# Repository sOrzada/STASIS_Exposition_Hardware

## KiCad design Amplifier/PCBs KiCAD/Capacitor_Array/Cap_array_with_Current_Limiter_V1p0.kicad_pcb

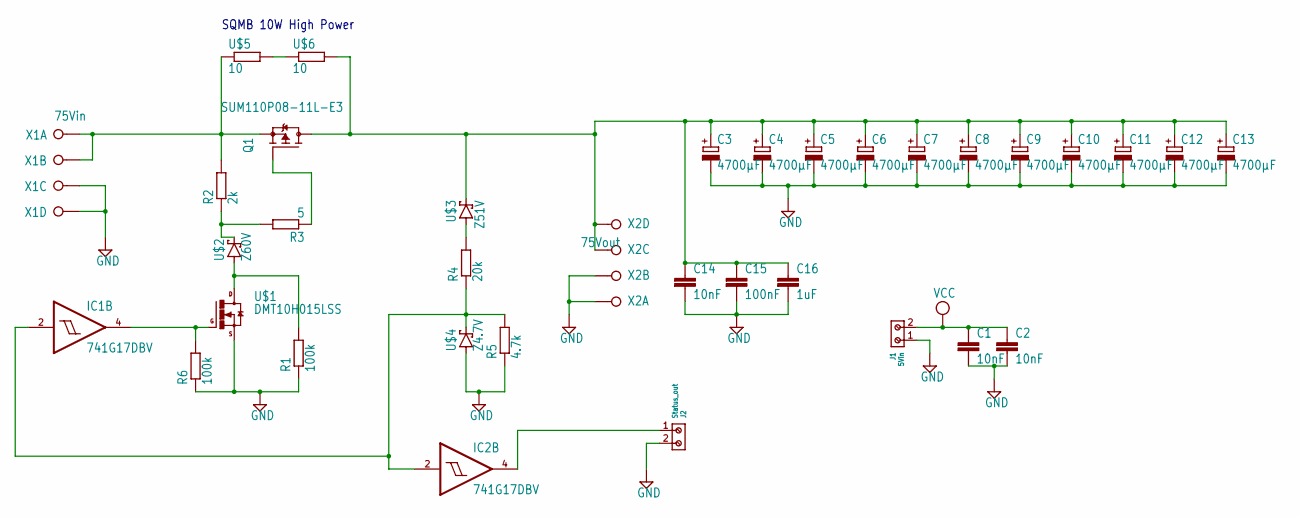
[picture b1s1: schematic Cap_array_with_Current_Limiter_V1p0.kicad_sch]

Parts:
C1, C2: 10nF; C0805
C3, C4, C5, C6, C7, C8, C9, C10, C11, C12, C13: 4700µF; EB30D
C14: 10nF; C1206
C15: 100nF; C1206
C16: 1uF; C1206
IC1, IC2: 741G17DBV; SOT23-5
J1: 5Vin; 691210910002
J2: Status_out; 691210910002
Q1: SUM110P08-11L-E3; TO263
R1, R6: 100k; R0805
R2: 2k; R2512
R3: 5; R0805
R4: 20k; R0805
R5: 4.7k; R0805
U$1: DMT10H015LSS; SOIC8
U$2: Z60V; DO-214AA
U$3: Z51V; DO-214AA
U$4: Z4.7V; DO-214AA
U$5, U$6: 10; SQMB
X1: 75Vin; W237-4P
X2: 75Vout; W237-4P

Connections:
GND: C1.2, C2.2, C3.-, C4.-, C5.-, C6.-, C7.-, C8.-, C9.-, C10.-, C11.-, C12.-, C13.-, C14.2, C15.2, C16.2, IC1.3 (GND), IC2.3 (GND), J1.1, J2.2, R1.1, R5.1, R6.1, U$1.1 (S), U$1.2 (S), U$1.3 (S), U$4.A, X1.3, X1.4, X2.1, X2.2
unnamed: R2.1, R3.2, U$2.C
unnamed: Q1.2 (S), R2.2, U$5.P$1 (1), X1.1, X1.2
unnamed: U$5.P$2 (2), U$6.P$1 (1)
unnamed: IC1.4 (O), R6.2, U$1.4 (G)
unnamed: Q1.1 (G), R3.1
unnamed: C3.+, C4.+, C5.+, C6.+, C7.+, C8.+, C9.+, C10.+, C11.+, C12.+, C13.+, C14.1, C15.1, C16.1, Q1.3 (D), U$3.C, U$6.P$2 (2), X2.3, X2.4
unnamed: R4.2, U$3.A
unnamed: IC1.2 (I), IC2.2 (I), R4.1, R5.2, U$4.C
unnamed: IC2.4 (O), J2.1
unnamed: R1.2, U$1.5 (D), U$1.6 (D), U$1.7 (D), U$1.8 (D), U$2.A
VCC: C1.1, C2.1, IC1.5 (VCC), IC2.5 (VCC), J1.2

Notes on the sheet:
SQMB 10W High Power

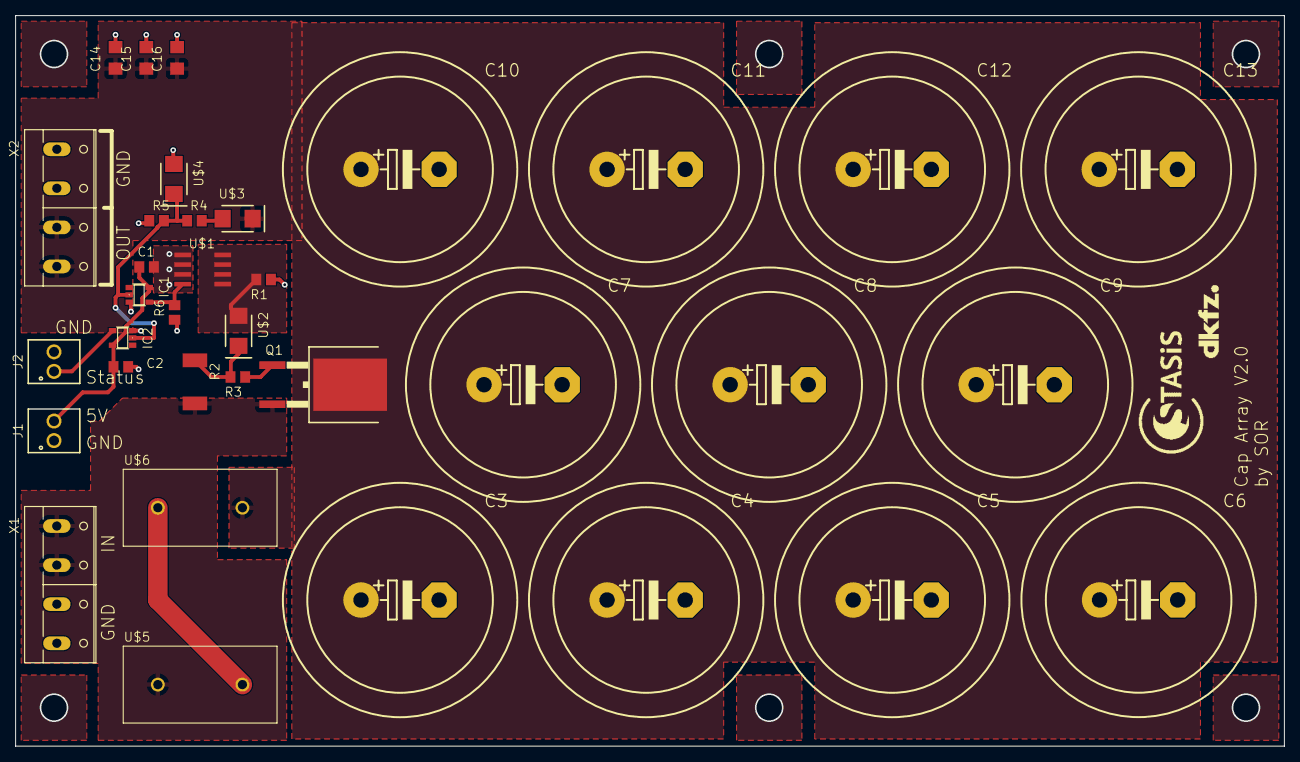
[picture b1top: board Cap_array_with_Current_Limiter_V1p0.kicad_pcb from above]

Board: 2 copper layers, 165.0 x 95.0 mm, 37 parts (0 on the bottom side), 12 nets.

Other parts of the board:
U$7: LOGO_STASIS
U$8: LOGO_DKFZ

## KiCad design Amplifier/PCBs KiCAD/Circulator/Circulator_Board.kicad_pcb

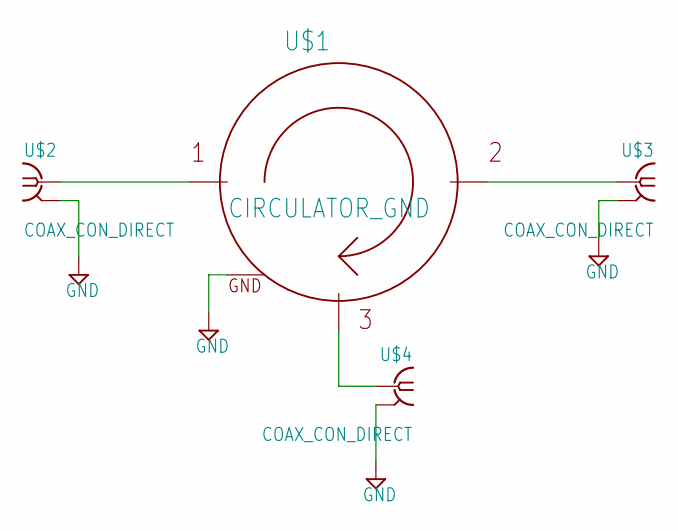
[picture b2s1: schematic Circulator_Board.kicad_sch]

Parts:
U$1: CIRCULATOR_GND; JCD0126T0130LC100
U$2, U$3, U$4: COAX_CON_DIRECT; COAX.141

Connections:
GND: U$1.P$1 (P$GND), U$1.P$2 (P$GND), U$1.P$3 (P$GND), U$1.P$4 (P$GND), U$2.P$2 (GND@1), U$3.P$2 (GND@1), U$4.P$2 (GND@1)
unnamed: U$1.P$IN, U$2.P$1 (1)
unnamed: U$1.P$OUT, U$3.P$1 (1)
unnamed: U$1.P$LOAD, U$4.P$1 (1)

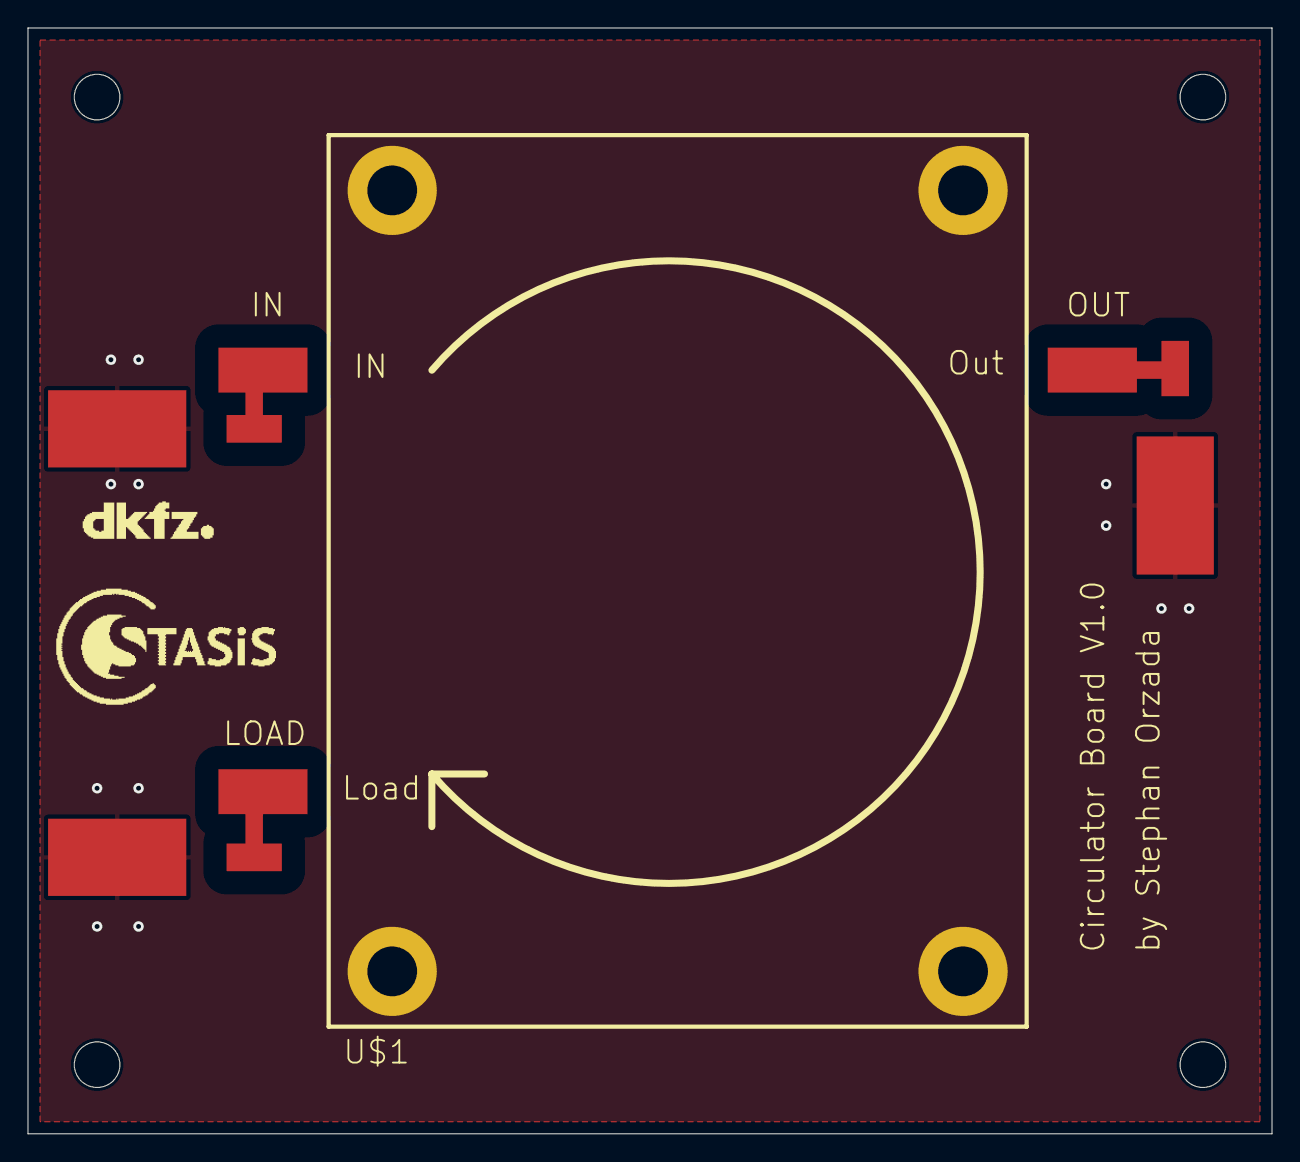
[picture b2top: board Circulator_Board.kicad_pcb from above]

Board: 2 copper layers, 90.0 x 80.0 mm, 10 parts (0 on the bottom side), 4 nets.

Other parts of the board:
@HOLE0, @HOLE1, @HOLE2, @HOLE3: (no value)
U$5: LOGO_DKFZ
U$6: LOGO_STASIS

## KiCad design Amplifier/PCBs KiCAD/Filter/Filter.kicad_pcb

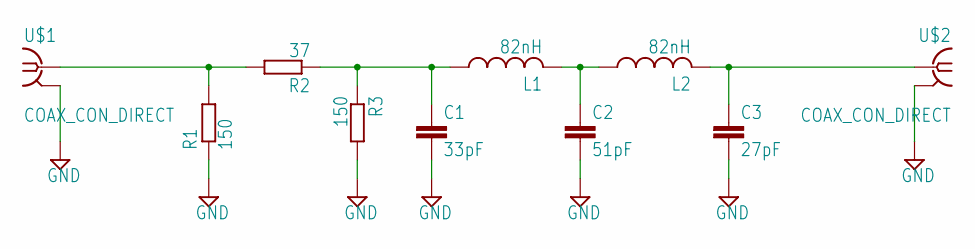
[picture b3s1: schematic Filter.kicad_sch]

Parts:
C1: 33pF; C0805
C2: 51pF; C0805
C3: 27pF; C0805
L1, L2: 82nH; L2012C
R1, R3: 150; R0805
R2: 37; R0805
U$1, U$2: COAX_CON_DIRECT; COAX.141

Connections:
GND: C1.2, C2.2, C3.2, R1.1, R3.2, U$1.P$2 (GND@1), U$2.P$2 (GND@1)
unnamed: C3.1, L2.2, U$2.P$1 (1)
unnamed: C2.1, L1.2, L2.1
unnamed: C1.1, L1.1, R2.1, R3.1
unnamed: R1.2, R2.2, U$1.P$1 (1)

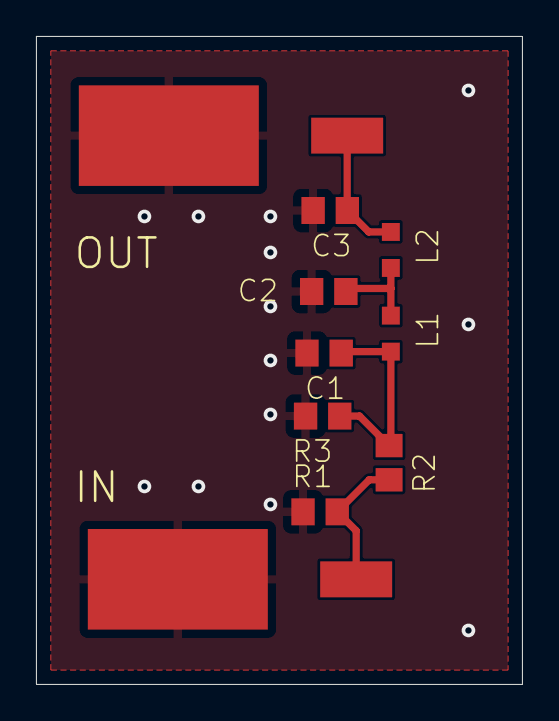
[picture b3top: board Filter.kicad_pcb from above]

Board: 2 copper layers, 27.0 x 36.0 mm, 10 parts (0 on the bottom side), 5 nets.

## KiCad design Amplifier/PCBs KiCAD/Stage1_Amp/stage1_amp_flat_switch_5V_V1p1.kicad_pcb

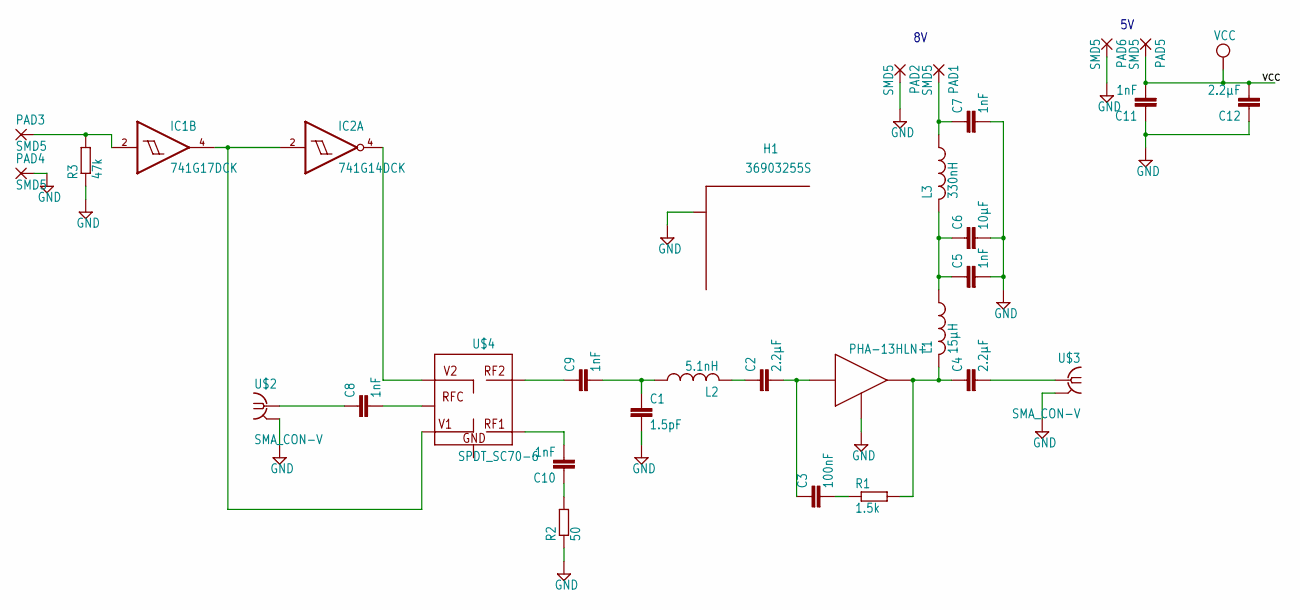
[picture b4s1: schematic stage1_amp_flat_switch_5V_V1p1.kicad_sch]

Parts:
C1: 1.5pF; C0402
C2, C4, C12: 2.2µF; C0402
C3: 100nF; C0402
C5, C7, C8, C9, C10, C11: 1nF; C0402
C6: 10µF; C0805
H1: 36903255S; WE-SHC_ONE-PIECE_36903255S
IC1: 741G17DCK; SC70-5
IC2: 741G14DCK; SC70-5
L1: 15µH; L3225M
L2: 5.1nH; L2012C
L3: 330nH; L3225M
PAD1, PAD2, PAD3, PAD4, PAD5, PAD6: SMD5; SMD2,54-5,08
R1: 1.5k; R0402
R2: 50; R0402
R3: 47k; R0805
U$1: PHA-13HLN+; SOT89
U$2, U$3: SMA_CON-V; BU-SMA-V
U$4: SPDT_SC70-6; SC70-6

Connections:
GND: C1.2, C5.2, C6.2, C7.2, C11.1, C12.1, H1.1, H1.2, H1.3, H1.4, H1.5, H1.6, H1.7, H1.8, H1.9, H1.10, H1.11, H1.12, H1.13, H1.14, H1.15, H1.16, H1.17, H1.18, H1.19, H1.20, IC1.3 (GND), IC2.3 (GND), PAD2.1, PAD4.1, PAD6.1, R2.1, R3.1, U$1.2 (GND), U$1.2@1 (GND), U$2.2 (GND@1), U$2.3 (GND@1), U$2.4 (GND@1), U$2.5 (GND@1), U$3.2 (GND@1), U$3.3 (GND@1), U$3.4 (GND@1), U$3.5 (GND@1)
unnamed: C2.1, L2.2
unnamed: C2.2, C3.1, U$1.1 (IN)
unnamed: C4.1, L1.2, R1.2, U$1.3 (OUT)
unnamed: C1.1, C9.2, L2.1
unnamed: C3.2, R1.1
unnamed: C4.2, U$3.1
unnamed: C5.1, C6.1, L1.1, L3.2
unnamed: C7.1, L3.1, PAD1.1
unnamed: C8.2, U$4.5 (RFC)
unnamed: C8.1, U$2.1
unnamed: C9.1, U$4.3 (RF2)
unnamed: C10.2, U$4.1 (RF1)
unnamed: C10.1, R2.2
unnamed: IC1.4 (O), IC2.2 (I), U$4.6 (V1)
unnamed: IC2.4 (O), U$4.4 (V2)
unnamed: IC1.2 (I), PAD3.1, R3.2
VCC: C11.2, C12.2, IC1.5 (VCC), IC2.5 (VCC), PAD5.1

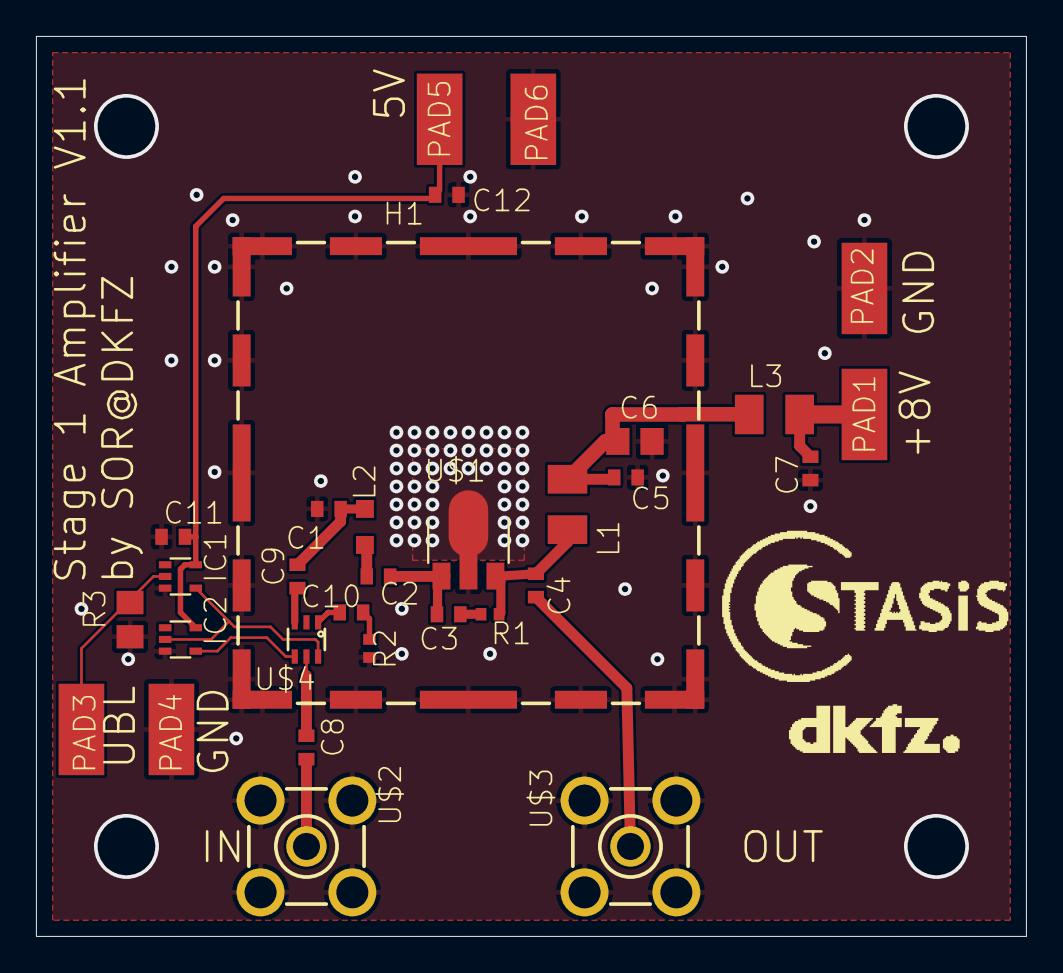
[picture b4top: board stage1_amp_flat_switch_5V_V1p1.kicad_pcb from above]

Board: 2 copper layers, 55.0 x 50.0 mm, 33 parts (0 on the bottom side), 18 nets.

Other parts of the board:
U$5: LOGO_DKFZ
U$6: LOGO_STASIS

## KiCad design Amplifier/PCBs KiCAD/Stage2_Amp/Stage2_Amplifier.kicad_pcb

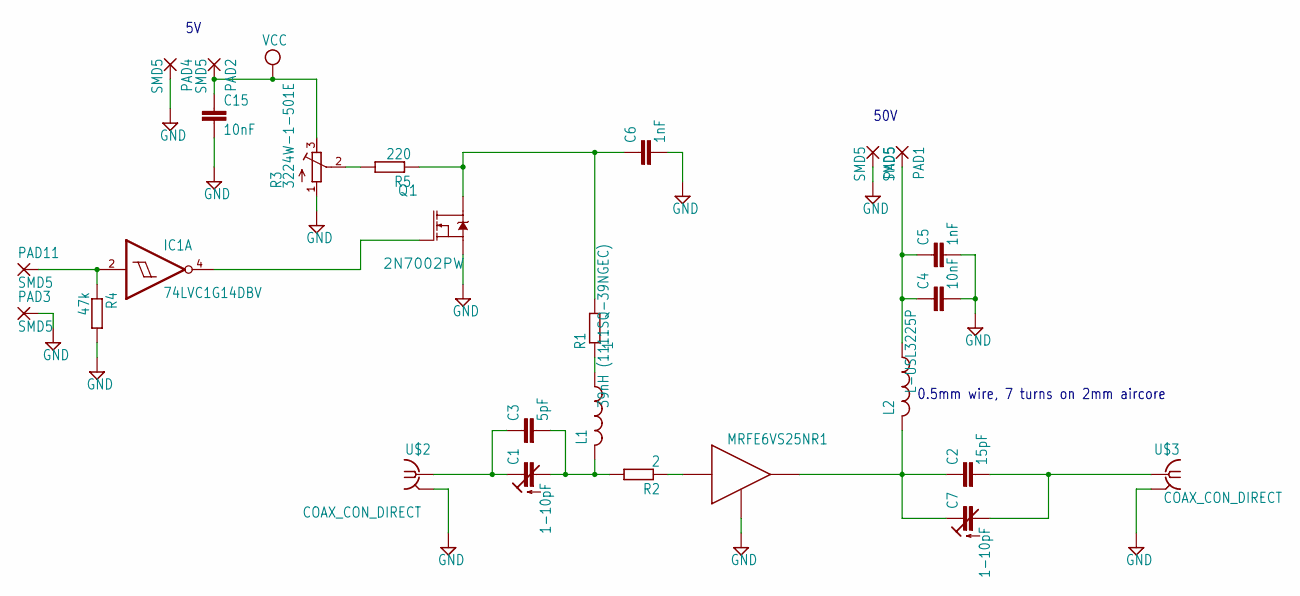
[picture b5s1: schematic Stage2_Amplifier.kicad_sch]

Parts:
C1, C7: 1-10pF; CTRIMTZBX4
C2: 15pF; C1210
C3: 5pF; C1210
C4: 10nF; C1206
C5: 1nF; C1206
C6: 1nF; C0805
C15: 10nF; C0805
IC1: 74LVC1G14DBV; SOT23-5
L1: 39nH (1111SQ-39NGEC); L3225P
L2: L-USL3225P; L3225P
PAD1, PAD2, PAD3, PAD4, PAD5, PAD11: SMD5; SMD2,54-5,08
Q1: 2N7002PW; SOT323
R1: 1; R1206
R2: 2; R1206
R3: 3224W-1-501E; RTRIM3224W
R4: 47k; R0805
R5: 220; R0805
U$1: MRFE6VS25NR1; TO-270_ONBOARD
U$2, U$3: COAX_CON_DIRECT; COAX.141

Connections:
GND: C4.2, C5.2, C6.2, C15.2, IC1.3 (GND), PAD3.1, PAD4.1, PAD5.1, Q1.2 (S), R3.1 (A), R4.2, U$1.P$3 (GND), U$2.P$2 (GND@1), U$3.P$2 (GND@1)
unnamed: R2.1, U$1.P$2 (IN)
unnamed: C1.2 (A), C3.2, L1.2, R2.2
unnamed: L1.1, R1.1
unnamed: C2.1, C7.1 (E), L2.2, U$1.P$1 (OUT)
unnamed: C1.1 (E), C3.1, U$2.P$1 (1)
unnamed: C2.2, C7.2 (A), U$3.P$1 (1)
unnamed: C4.1, C5.1, L2.1, PAD1.1
unnamed: C6.1, Q1.3 (D), R1.2, R5.1
unnamed: R3.2 (S), R5.2
unnamed: IC1.4 (O), Q1.1 (G)
unnamed: IC1.2 (I), PAD11.1, R4.1
VCC: C15.1, IC1.5 (VCC), PAD2.1, R3.3 (E)

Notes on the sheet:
50V
0.5mm wire, 7 turns on 2mm aircore

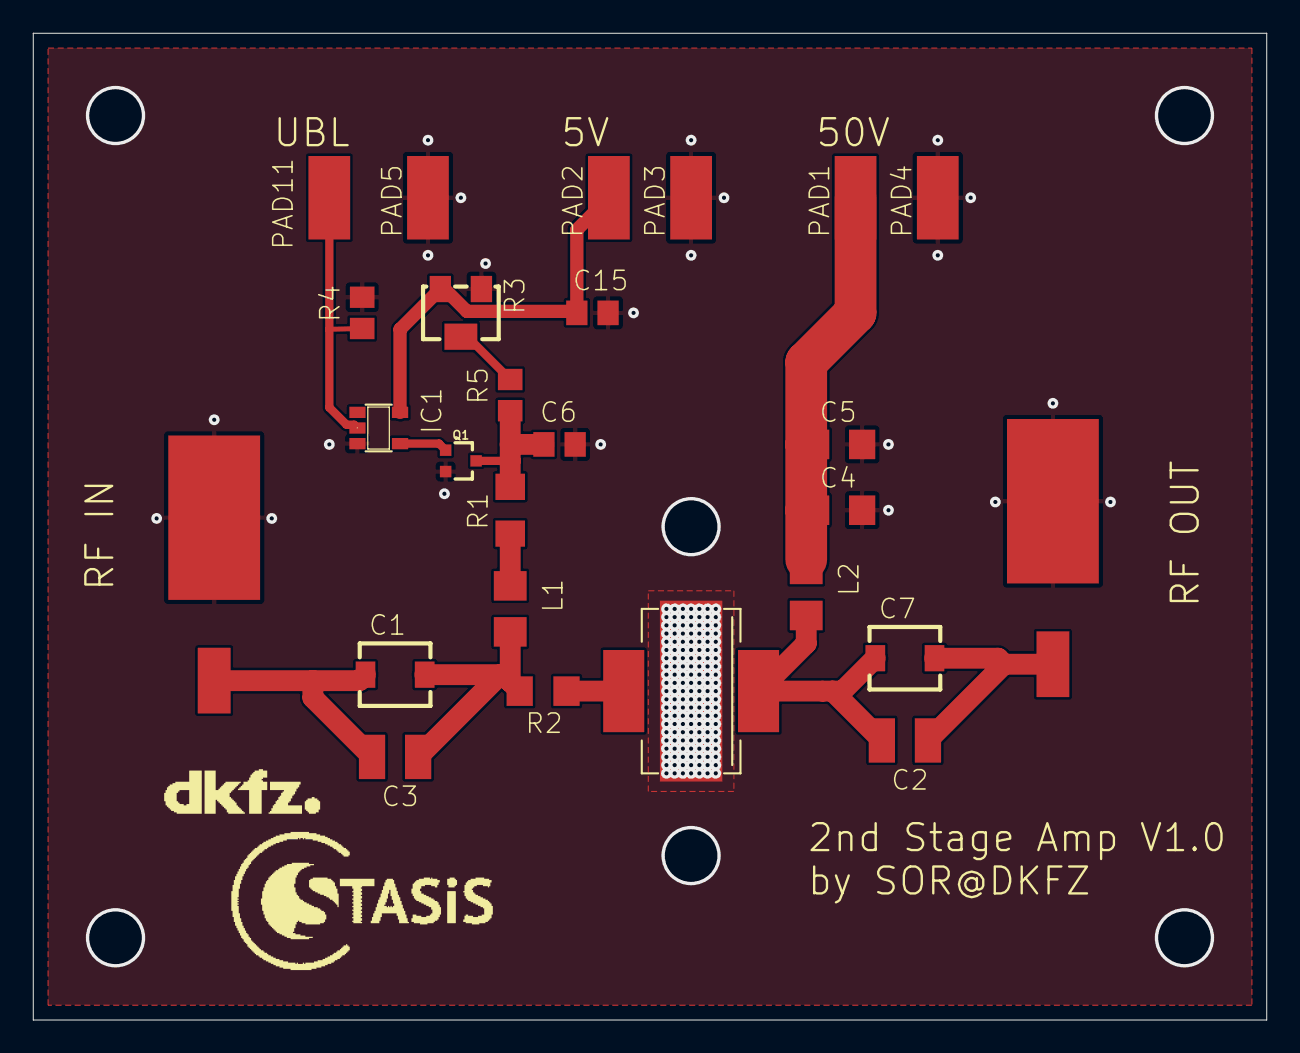
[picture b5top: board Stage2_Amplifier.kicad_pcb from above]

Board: 2 copper layers, 75.0 x 60.0 mm, 28 parts (0 on the bottom side), 13 nets.

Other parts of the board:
U$4: LOGO_STASIS
U$5: LOGO_DKFZ

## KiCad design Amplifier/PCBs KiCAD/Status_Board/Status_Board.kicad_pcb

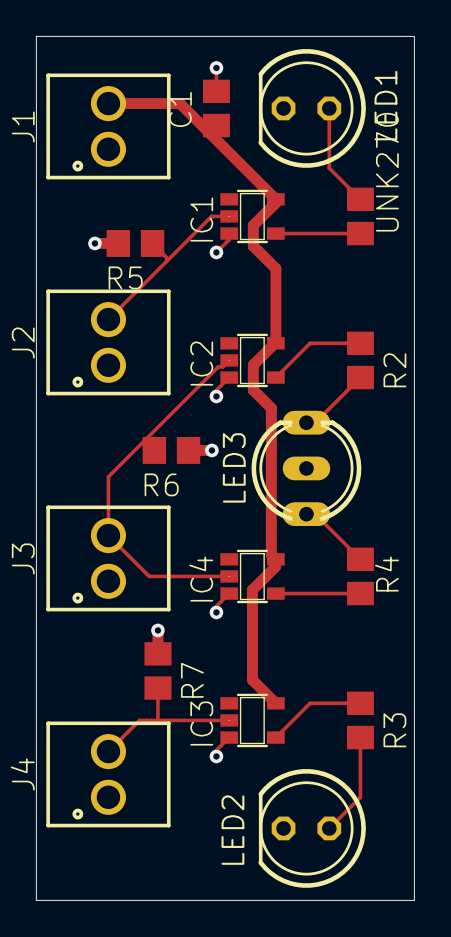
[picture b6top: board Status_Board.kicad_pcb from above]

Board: 2 copper layers, 21.0 x 48.0 mm, 19 parts (0 on the bottom side), 13 nets.

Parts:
C1: 10nF; C0805_334
IC1, IC2, IC3: 74LVC1G17DBV; SOT23-5_87
IC4: 74LVC1G14DBV; SOT23-5_87
J1: 5V; 691210910002_16280519
J2: 75V_Status; 691210910002_16280519
J3: Amp_State; 691210910002_16280519
J4: UBL; 691210910002_16280519
LED1, LED2: LED5MM_259
LED3: DUOLED-C-5MM_259
R2, R3: 220; R0805_334
R4: 180; R0805_334
R5, R6, R7: 47k; R0805_334
UNK270: R0805_334

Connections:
GND: C1.2, IC1.3, IC2.3, IC3.3, IC4.3, J1.1, J2.1, J3.1, J4.1, LED1.K, LED2.K, LED3.C, R5.2, R6.1, R7.1
unnamed: IC4.4, R4.1
unnamed: IC1.2, J2.2, R5.1
unnamed: IC2.2, IC4.2, J3.2, R6.2
unnamed: IC3.2, J4.2, R7.2
unnamed: IC1.4, UNK270.1
unnamed: IC2.4, R2.1
unnamed: IC3.4, R3.1
unnamed: LED1.A, UNK270.2
unnamed: LED3.AR, R2.2
unnamed: LED2.A, R3.2
unnamed: LED3.AX, R4.2
VCC: C1.1, IC1.5, IC2.5, IC3.5, IC4.5, J1.2

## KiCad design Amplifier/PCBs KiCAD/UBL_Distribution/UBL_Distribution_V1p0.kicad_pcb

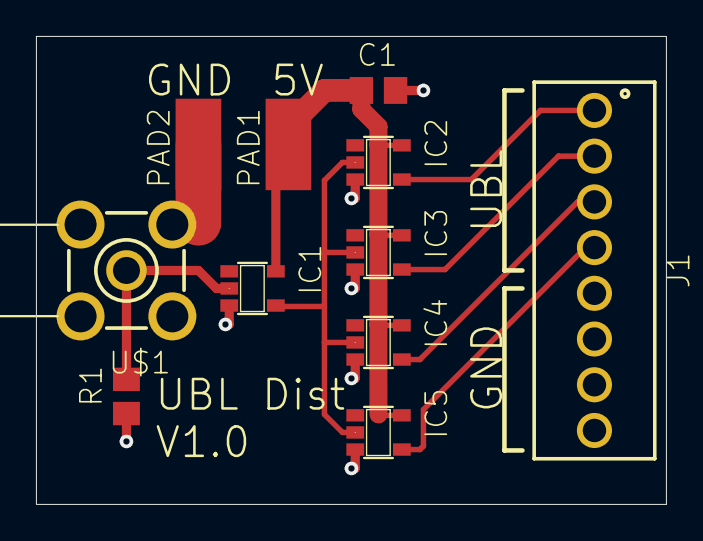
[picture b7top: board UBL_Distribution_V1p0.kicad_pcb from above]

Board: 2 copper layers, 35.0 x 26.0 mm, 11 parts (0 on the bottom side), 8 nets.

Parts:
C1: 10nF; C0805_334
IC1, IC2, IC3, IC4, IC5: 74LVC1G17DBV; SOT23-5_87
J1: Unblank; 691210910008_16280519
PAD1: 5V; SMD2,54-5,08_412
PAD2: GND; SMD2,54-5,08_412
R1: 47k; R0805_334
U$1: SMA_CON-H; BU-SMA-H

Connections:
GND: C1.2, IC1.3, IC2.3, IC3.3, IC4.3, IC5.3, J1.5, J1.6, J1.7, J1.8, PAD2.1, R1.1, U$1.2, U$1.3, U$1.4, U$1.5
unnamed: IC1.2, R1.2, U$1.1
unnamed: IC1.4, IC2.2, IC3.2, IC4.2, IC5.2
unnamed: IC2.4, J1.1
unnamed: IC3.4, J1.2
unnamed: IC4.4, J1.3
unnamed: IC5.4, J1.4
VCC: C1.1, IC1.5, IC2.5, IC3.5, IC4.5, IC5.5, PAD1.1

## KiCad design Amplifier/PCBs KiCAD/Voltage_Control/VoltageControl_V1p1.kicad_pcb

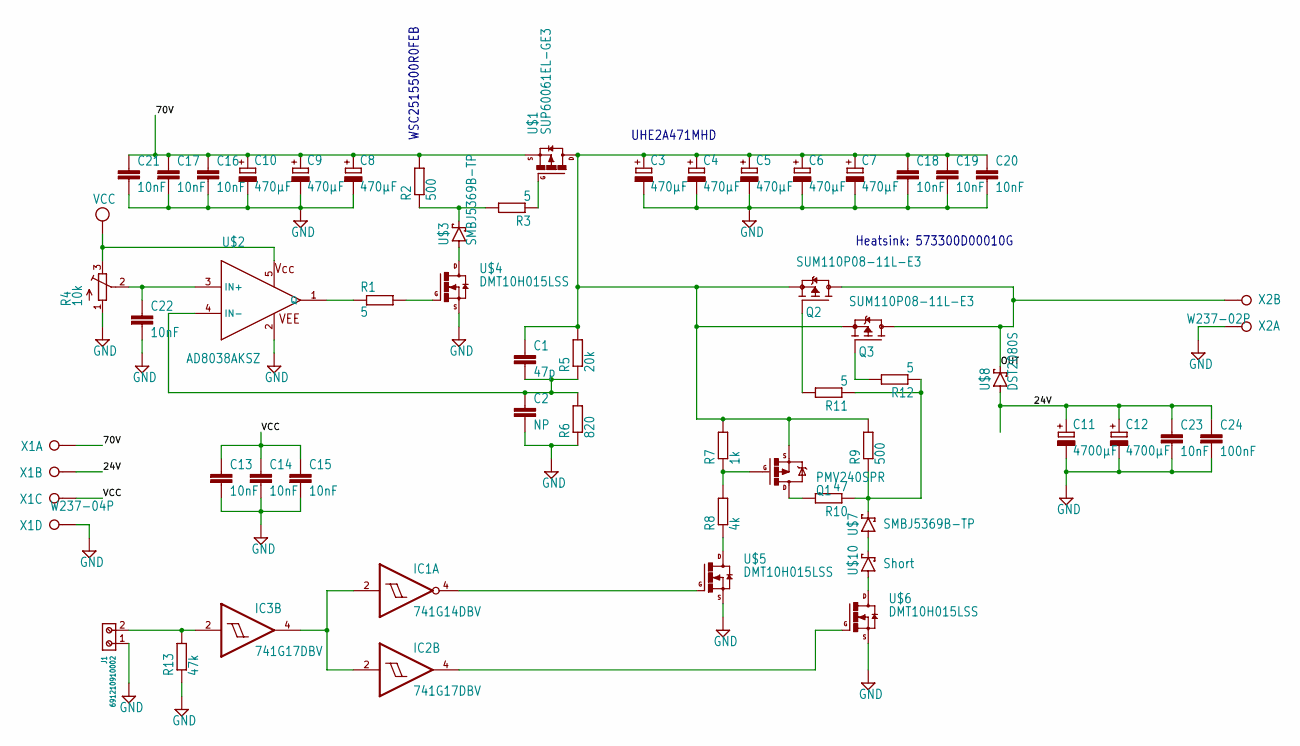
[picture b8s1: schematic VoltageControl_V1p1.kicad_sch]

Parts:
C1: 47p; C0805
C2: NP; C0805
C3, C4, C5, C6, C7, C8, C9, C10: 470µF; E7,5-16
C11, C12: 4700µF; E7,5-18
C13, C14, C15, C16, C17, C18, C19, C20, C21, C22: 10nF; C0805
C23: 10nF; C1206
C24: 100nF; C1206
IC1: 741G14DBV; SOT23-5
IC2, IC3: 741G17DBV; SOT23-5
J1: 691210910002
Q1: PMV240SPR; SOT23-3
Q2, Q3: SUM110P08-11L-E3; TO263
R1, R3, R11, R12: 5; R0805
R2, R9: 500; R2512
R4: 10k; SM-42_43X
R5: 20k; R0805
R6: 820; R0805
R7: 1k; R2512
R8: 4k; R2512
R10: 47; R0805
R13: 47k; R0805
U$1: SUP60061EL-GE3; TO220BH
U$2: AD8038AKSZ; SC70-5
U$3, U$7: SMBJ5369B-TP; DO-214AA
U$4, U$5, U$6: DMT10H015LSS; SOIC8
U$8: DST2080S; TO-277B
U$10: Short; DO-214AA
X1: W237-04P; W237-4P
X2: W237-02P; W237-132

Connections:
24V: C11.+, C12.+, C23.1, C24.1, U$8.P$2 (A), U$8.P$3 (A), X1.2
70V: C8.+, C9.+, C10.+, C16.1, C17.1, C21.1, R2.2, U$1.P$3 (S), X1.1
GND: C2.2, C3.-, C4.-, C5.-, C6.-, C7.-, C8.-, C9.-, C10.-, C11.-, C12.-, C13.2, C14.2, C15.2, C16.2, C17.2, C18.2, C19.2, C20.2, C21.2, C22.2, C23.2, C24.2, IC1.3 (GND), IC2.3 (GND), IC3.3 (GND), J1.1, R4.1 (A), R6.1, R13.1, U$2.2 (VEE), U$4.1 (S), U$4.2 (S), U$4.3 (S), U$5.1 (S), U$5.2 (S), U$5.3 (S), U$6.1 (S), U$6.2 (S), U$6.3 (S), X1.4, X2.1
unnamed: R1.1, U$2.1 (Q)
unnamed: R1.2, U$4.4 (G)
unnamed: U$3.A, U$4.5 (D), U$4.6 (D), U$4.7 (D), U$4.8 (D)
unnamed: R2.1, R3.2, U$3.C
unnamed: R3.1, U$1.P$1 (G)
unnamed: U$7.A, U$10.C
unnamed: C22.1, R4.2 (S), U$2.3 (IN+)
unnamed: C1.2, C2.1, R5.1, R6.2, U$2.4 (IN-)
unnamed: Q1.1 (G), R7.1, R8.2
unnamed: C1.1, C3.+, C4.+, C5.+, C6.+, C7.+, C18.1, C19.1, C20.1, Q1.2 (S), Q2.2 (S), Q3.2 (S), R5.2, R7.2, R9.2, U$1.P$2 (D)
unnamed: IC2.4 (O), U$6.4 (G)
unnamed: R8.1, U$5.5 (D), U$5.6 (D), U$5.7 (D), U$5.8 (D)
unnamed: U$6.5 (D), U$6.6 (D), U$6.7 (D), U$6.8 (D), U$10.A
unnamed: R9.1, R10.1, R11.1, R12.1, U$7.C
unnamed: Q1.3 (D), R10.2
unnamed: Q2.1 (G), R11.2
unnamed: Q3.1 (G), R12.2
unnamed: IC1.2 (I), IC2.2 (I), IC3.4 (O)
unnamed: IC1.4 (O), U$5.4 (G)
unnamed: IC3.2 (I), J1.2, R13.2
OUT: Q2.3 (D), Q3.3 (D), U$8.P$1 (C), X2.2
VCC: C13.1, C14.1, C15.1, IC1.5 (VCC), IC2.5 (VCC), IC3.5 (VCC), R4.3 (E), U$2.5 (VCC), X1.3

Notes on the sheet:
Heatsink: 573300D00010G
WSC2515500R0FEB
UHE2A471MHD

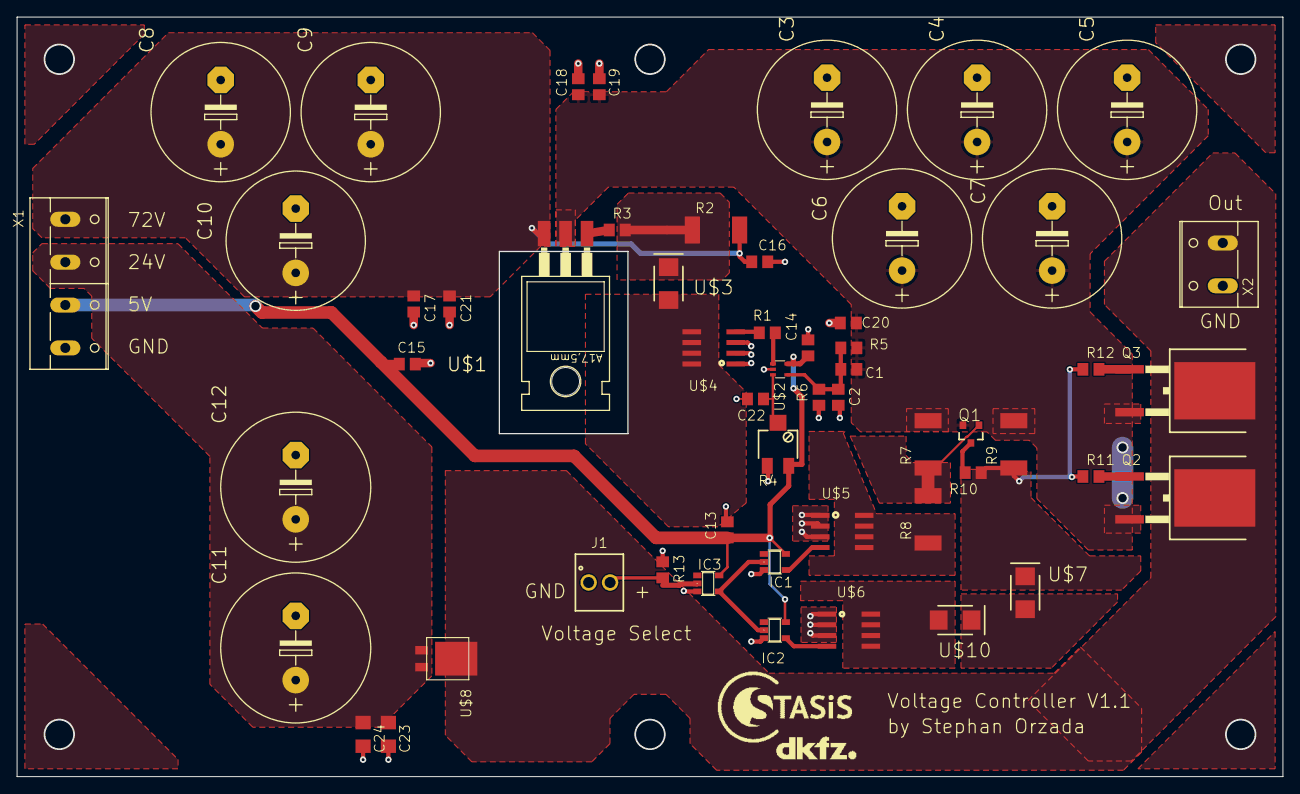
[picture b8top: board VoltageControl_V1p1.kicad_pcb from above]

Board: 2 copper layers, 150.0 x 90.0 mm, 57 parts (0 on the bottom side), 25 nets.

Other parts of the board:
U$11: LOGO_STASIS
U$12: LOGO_DKFZ
